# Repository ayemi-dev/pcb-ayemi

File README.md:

# Placas abiertas de Ayemi

Tres placas educativas de hardware libre, una por familia de microcontrolador. Cada una ya trae soldados LED, botones, zumbador, perilla y sensores, y tiene conectores de 4 pines para módulos. Aquí está todo para estudiarlas, modificarlas o fabricarlas: KiCad, Gerber, lista de piezas, firmware de demostración y las herramientas que las generan.

Fichas y renders: [ayemi.org/pcb](https://ayemi.org/pcb)

| Placa | Para quién | Micro | Medida | Carpeta |
|---|---|---|---|---|
| **Chispa por Ayemi** | De 10 a 15 años | ATmega328P (compatible con el IDE de Arduino, placa Uno) | 90 × 60 mm | [`placas/entrenamiento-328p`](placas/entrenamiento-328p) |
| **Enlace por Ayemi** | Secundaria y preparatoria | ESP32-S3 con WiFi y Bluetooth LE, sensor de temperatura y humedad | 90 × 60 mm | [`placas/enlace-esp32s3`](placas/enlace-esp32s3) |
| **Impulso por Ayemi** | Universidad | STM32F411 con USB nativo, SWD, sensor de movimiento y microSD | 100 × 70 mm | [`placas/impulso-stm32`](placas/impulso-stm32) |

## Estado

Las tres están en **Diseño completo**: el esquemático y la placa pasan las revisiones de KiCad (ERC y DRC) sin errores, tienen renders y su firmware de demostración compila. **Todavía no se han fabricado ni probado en físico.** Antes de pedirlas, lee la sección «Pendiente antes de fabricar» del README de cada placa.

| Peldaño | Qué significa |
|---|---|
| Diseño completo | ERC y DRC en 0, renders y firmware que compila |
| Diseño verificado | Además, el análisis DFM de JLCPCB aprobado: lista para fabricar |
| Fabricada y probada | Fabricada y probada en banco con su firmware |

## Qué hay en cada placa

| Carpeta | Contenido |
|---|---|
| `README.md` | Mapa de pines, conectores, cómo programarla y avisos |
| `*.kicad_sch`, `*.kicad_pcb` | Proyecto de KiCad 10 |
| `spec/` | La fuente de verdad: cada hoja del esquemático y la placa descritas en YAML |
| `lib/` | Huellas y modelos 3D propios |
| `fab/v0.1/` | Gerber, BOM y CPL para JLCPCB, esquemático en PDF y serigrafía a escala 1:1 |
| `firmware/` | Demo y prueba de las salidas |
| `docs/` | Diagrama de pines y renders |
| `reportes/` | ERC, DRC, existencias de las piezas, ruteo y modelos 3D |

## Cómo se generan

Las placas no se dibujan a mano: los scripts de `tools/` leen los YAML de `spec/` y generan el esquemático, colocan y rutean la placa, ponen la serigrafía y sacan los archivos de fabricación. Necesitas KiCad 10 y Python 3.12 con `pyyaml` y `segno`. Los pasos exactos de cada placa están en su README, en «Cómo fabricarla».

## Licencias

- Hardware (esquemáticos, placa, Gerber, BOM, modelos 3D): [CERN-OHL-S-2.0](LICENSES/CERN-OHL-S-2.0.txt)
- Firmware y ejemplos: [MIT](LICENSES/MIT.txt)
- Documentación: [CC BY-SA 4.0](LICENSES/CC-BY-SA-4.0.txt)

El nombre y el logotipo **Ayemi** no se incluyen en ninguna de estas licencias: quedan reservados. Detalle en [`LICENSES/LEEME.md`](LICENSES/LEEME.md).

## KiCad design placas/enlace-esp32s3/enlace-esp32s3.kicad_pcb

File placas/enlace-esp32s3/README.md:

# Enlace por Ayemi · v0.1 (ESP32-S3)

**Enlace por Ayemi** es una placa de 90 × 60 mm, de dos capas, para secundaria y preparatoria: lleva un módulo ESP32-S3-WROOM-1-N8 con WiFi y Bluetooth LE, USB-C directo al micro, un sensor de temperatura y humedad SHT40, y ya trae soldados tres LED, un LED RGB, dos botones, un zumbador, una perilla y un sensor de luz. Tiene cinco conectores de 4 pines (I2C 1, I2C 2, SERIE, ANALÓGICO 1 y 2), un conector para pantalla OLED y dos headers con los pines libres. Se programa desde el IDE de Arduino con el núcleo `esp32` de Espressif.

## Estado de la versión 0.1

| Punto | Estado |
|---|---|
| Esquemático (ERC) | 0 errores y 0 advertencias |
| Placa (DRC, con paridad contra el esquemático) | 0 errores, 0 conexiones sin hacer; 2 advertencias de serigrafía justificadas en `spec/drc_justificaciones.yaml` |
| BOM y CPL | 34 números de LCSC (15 Basic y 19 Extended) y 65 componentes; todos con existencia para 50 placas (consulta del 2026-11-02, `reportes/existencias.md`) |
| Renders | Cuatro, con fondo transparente: `superior`, `inferior`, `isometrico` y `portada` (3168 px de ancho, a 45°), en `docs/renders/`. Todas las piezas tienen modelo 3D; siete son cajas o cilindros sencillos (`reportes/modelos3d.md`) |
| Firmware de demo | Compila para «ESP32S3 Dev Module» con USB CDC: 947 953 bytes de flash (72 %) y 42 976 de RAM (13 %). No se ha probado en una placa |
| QR de la cara inferior | Se lee en el render y devuelve `https://ayemi.org/p/esp32` |

**Estado: Diseño completo.** Cumple ERC en 0, DRC en 0, renders completos y firmware que compila. No es «Diseño verificado» (falta el análisis DFM de JLCPCB con su captura) ni «Fabricada y probada» (no hay placa física). No se fabrica por ahora.

## Pendiente antes de fabricar

El rigor que se dejó para después del cierre rápido. Nada de esto está hecho, y la placa no debe fabricarse sin resolverlo:

1. **Antena.** El módulo está a 90 × 60 mm con la antena hacia el borde inferior y una zona sin cobre de 19.6 × 7.7 mm bajo ella, en las dos caras. La hoja del módulo pide 15 mm de aire alrededor de la antena y aquí no se cumplen: el USB-C queda a la izquierda y el DIP a la derecha, ambos a pocos milímetros. El alcance del WiFi hay que medirlo en una placa real.
2. **Huellas locales.** `lib/ayemi.pretty/` trae dos copias de huellas oficiales de KiCad: el módulo, sin las vías térmicas de 0.2 mm (bajo el mínimo de 0.3 mm de JLCPCB), sin la zona de exclusión de cobre y con la cortesía reducida al cuerpo; y el SHT40, sin su zona de exclusión de cobre en la cara superior. Sin esa zona hay pistas pegadas al sensor y el módulo calienta la placa: la lectura de temperatura saldrá alta y hay que medir cuánto.
3. **Hojas de datos.** Leídas solo las de los LED KT-0603-R, -G y -Y (copia de rcscomponents.kiev.ua) y la del TEMT6000X01. No leídas: ESP32-S3-WROOM-1, AP7361C, SHT40, USBLC6, S8050, 2N7002 (falta confirmar que 3.3 V de compuerta lo enciende del todo, su `Vgs(th)` máximo) ni el RGB SZYY1209RGB-B. La Vf del LED verde amarillento KT-0603YG (C2289) y la del RGB salen del listado de JLCPCB, porque lcsc.com no dejó descargar sus hojas.
4. **Huellas provisionales**, a comparar con la hoja de datos o con la pieza física: RGB (D304: huella Avago PLCC4, pero el SZYY1209RGB-B de 3.2 × 2.7 mm tiene dimensiones inconsistentes con su nombre; orden de pines y pin 1 sin comprobar), fototransistor (Q302: polaridad del 1206), zumbador (BZ301), DIP (SW303: patrón del Omron A6S para la pieza Hanbo DO-10PT) y los conectores JST de 4 pines. Lista en `fab/v0.1/revisar_preview_v0.1.txt`.
5. **Modelos 3D sencillos.** USB-C, conectores JST, zumbador, potenciómetro, RGB, Q302 y SHT40 son cajas o cilindros; las medidas salen de la huella o de listados de distribuidor (fuentes en `reportes/modelos3d.md`). Las alturas del RGB (1.9 mm), del SHT40 (0.5 mm) y del zumbador (3.0 mm) son estimadas.
6. **Potencia.** El regulador AP7361C en SOT-223R disipa hasta 0.81 W en un pico de WiFi con `θJA` supuesto de 100 °C/W; el pico total (0.49 A) queda en el límite del PTC de 500 mA. Hay que medir ambos.
7. **USB.** D+ y D− van con pista de 0.2 mm en una ventana fina junto al conector; no se midió su longitud ni su impedancia.
8. **JLCPCB.** Falta subir los Gerber, la BOM y la CPL: análisis DFM con captura, vista previa del ensamblado (rotación de cada pieza en `rotacion_jlc`, hoy vacío), cotización y la decisión sobre el ensamblado de agujero pasante (J406, J407, J408 y RV301).
9. **Impresión a 1:1** de `fab/v0.1/serigrafia_1a1_v0.1_superior.pdf` e `_inferior.pdf`. Rótulos de 1.0 mm de alto. Emi va en versión de cabeza.
10. **Firmware y pruebas.** El demo solo se compiló. Faltan la prueba en placa, el proyecto de Wokwi y la pantalla OLED (el conector PANTALLA no tiene ejemplo).

## Mapa de pines

Con los diez interruptores del DIP (SW303; nueve en uso, la posición 10 queda sin conexión) en ON, cada periférico queda conectado a su pin. Con el interruptor en OFF, el pin queda libre para cables o módulos.

| Periférico | Pin | Posición del DIP | Notas |
|---|---|---|---|
| LED rojo | IO10 | 1 | |
| LED verde amarillento | IO11 | 2 | |
| LED amarillo | IO12 | 3 | |
| RGB rojo | IO13 | 4 | Ánodo común a 5 V, un 2N7002 por canal: pin en alto = encendido; PWM con `analogWrite` |
| RGB verde | IO14 | 5 | |
| RGB azul | IO15 | 6 | |
| Botón A | IO16 | 7 | 330 Ω en serie, sin pull-up externo: usa `INPUT_PULLUP`; vale 0 al pulsar |
| Botón B | IO17 | 8 | Igual que el A |
| Zumbador | IO18 | 9 | A la base de un S8050, desde 5 V; con `tone()` |
| Perilla | IO1 | sin DIP | ADC1, 1 kΩ en serie |
| Sensor de luz (TEMT6000) | IO2 | sin DIP | ADC1; más luz, más voltaje |
| SHT40 | IO8 (SDA), IO9 (SCL) | sin DIP | I2C, dirección 0x44, siempre conectado al bus |
| BOOT / RESET | IO0 / EN | botones | |

### Conectores

| Conector | Pines (de 1 a 4) |
|---|---|
| I2C 1 e I2C 2 (J401, J402, en paralelo) | SCL (IO9), SDA (IO8), 3V3, GND |
| SERIE (J403) | RX (IO44), TX (IO43), 3V3, GND |
| ANALÓGICO 1 (J404) | IO4, IO5, 3V3, GND |
| ANALÓGICO 2 (J405) | IO6, IO7, 3V3, GND |
| PANTALLA (J406, header de 4) | GND, 3V3, SCL (IO9), SDA (IO8) |
| IO A (J407, header de 10) | IO10 a IO18 y GND |
| IO B (J408, header de 12) | IO21, IO38, IO39, IO40, IO41, IO42, IO47, IO48, 3V3, 5V, GND, GND |

Pines que no salen a ningún lado: IO3, IO35 a IO37, IO45 e IO46 (de arranque o de la memoria del módulo). El diagrama de pines está en `docs/diagrama_pines.svg` y los renders en `docs/renders/`.

## Cómo programarla

1. Instala el IDE de Arduino y, desde el gestor de placas, el paquete **esp32** de Espressif (probado con 3.0.3).
2. Conecta la placa con un cable USB-C. Para cargar el primer programa mantén BOOT, pulsa RESET y suelta ambos.
3. En el IDE elige la placa «ESP32S3 Dev Module», con **USB CDC On Boot: Enabled**, y el puerto que aparece.
4. Abre `firmware/enlace_demo/enlace_demo.ino` y súbelo. Abre el monitor serie a 115200 baudios.

El demo prueba las salidas al encender, crea la red WiFi `Enlace-XXXX` (sin contraseña) y muestra en `http://192.168.4.1` la perilla, la luz, la temperatura, la humedad y los botones, y deja encender los LED, elegir el color del RGB y hacer sonar el zumbador.

Por línea de comandos: `arduino-cli compile --fqbn esp32:esp32:esp32s3:CDCOnBoot=cdc firmware/enlace_demo`.

## Avisos

- **Reservado: no uses IO19 ni IO20** (son el USB), ni IO0, IO3, IO45 e IO46 (arranque).
- **Conector SERIE.** Usa el UART0 (IO43 e IO44). Con USB CDC al arrancar, el monitor serie sale por el USB y el UART0 queda libre.
- **DIP en ON.** IO10 a IO18 quedan cargados por el periférico. Si conectas un módulo a uno de esos pines, pon su interruptor en OFF.
- **5 V.** Salen del USB después de un PTC de 500 mA. Los pines de datos son de 3.3 V y no toleran 5 V.
- **WiFi y consumo.** Un pico de transmisión pide hasta 355 mA al módulo. Con un cable largo o un hub el puerto puede entregar menos de 5 V.

## Cómo fabricarla

La fuente de verdad son los YAML de `spec/`. Los scripts de `tools/` generan y verifican todo lo demás; con KiCad cerrado:

```powershell
py -3.12 -P tools/gen_hoja.py placas/enlace-esp32s3 --todas       # esquemático
py -3.12 -P tools/erc.py placas/enlace-esp32s3                    # ERC
py -3.12 -P tools/huellas_locales.py placas/enlace-esp32s3        # copias ajustadas de huellas
powershell -File tools/construir_placa.ps1 -Placa placas/enlace-esp32s3 -Setup   # colocar, rutear, costura, serigrafía (30 a 40 min)
py -3.12 -P tools/drc.py placas/enlace-esp32s3                    # DRC
py -3.12 -P tools/fab.py placas/enlace-esp32s3                    # Gerber, BOM, CPL, PDF
py -3.12 -P tools/verificar_existencias.py placas/enlace-esp32s3
py -3.12 -P tools/renders.py placas/enlace-esp32s3                # superior, inferior, isométrico y portada
```

En `fab/v0.1/` quedan `gerbers_v0.1.zip`, `bom_jlc_v0.1.csv`, `cpl_jlc_v0.1.csv`, `esquematico_v0.1.pdf`, `revisar_preview_v0.1.txt` y los PDF de serigrafía a escala 1:1. La placa es de 2 capas, FR-4 de 1.6 mm, máscara negra y serigrafía blanca.

## Carpetas

| Carpeta | Contenido |
|---|---|
| `spec/` | YAML de cada hoja y de la placa; `logos/` con el logotipo, Emi y el QR |
| `lib/ayemi.pretty/` | Huellas locales (módulo y SHT40) |
| `lib/ayemi.3dshapes/` | Modelos 3D sencillos (`.wrl`) de las piezas sin modelo |
| `fab/v0.1/` | Archivos para JLCPCB y serigrafía 1:1 |
| `firmware/enlace_demo/` | Demo y prueba de fábrica |
| `docs/` | Diagrama de pines y renders |
| `reportes/` | ERC, DRC, existencias, ruteo y 3D |

## Licencias

- Hardware (esquemáticos, placa, Gerber, BOM, modelos 3D): CERN-OHL-S-2.0 (`../../LICENSES/CERN-OHL-S-2.0.txt`).
- Firmware y ejemplos: MIT (`firmware/LICENSE` y `../../LICENSES/MIT.txt`).
- Documentación y guías: CC BY-SA 4.0 (`../../LICENSES/CC-BY-SA-4.0.txt`).

El nombre y el logotipo **Ayemi** no se incluyen en ninguna de estas licencias: quedan reservados.

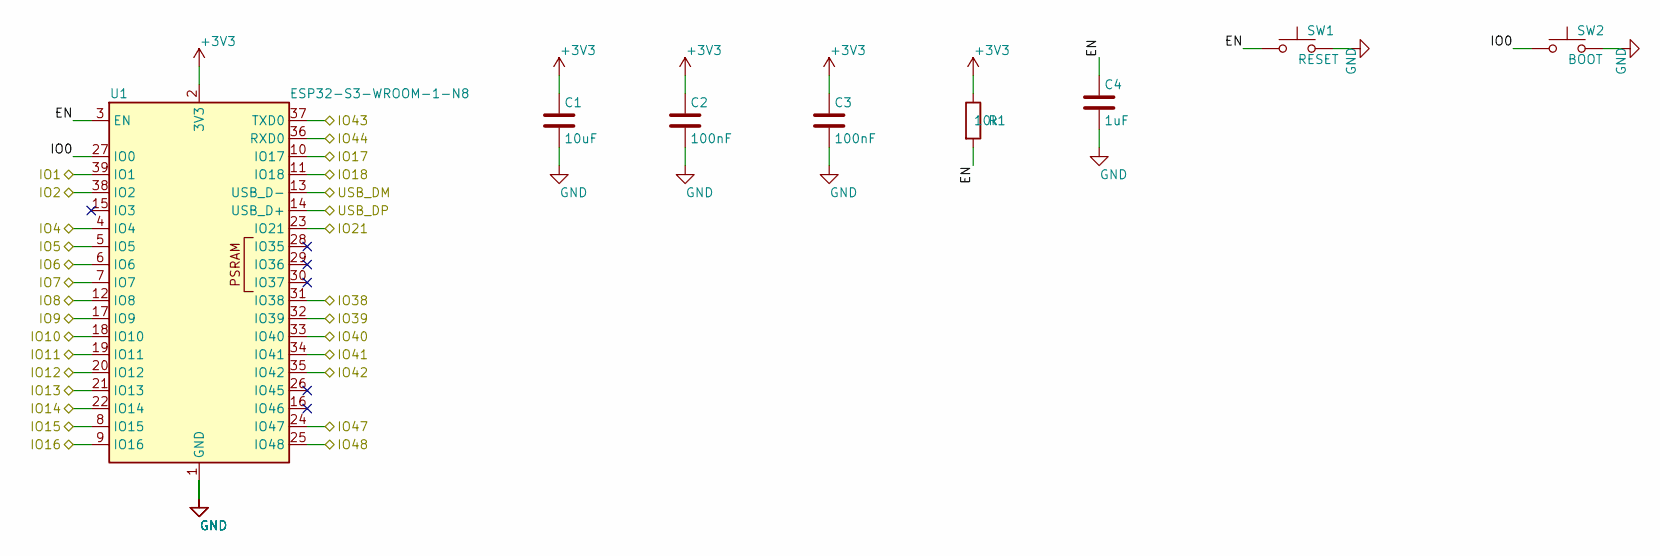
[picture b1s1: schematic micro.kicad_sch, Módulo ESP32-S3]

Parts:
C1: 10uF; C_0603_1608Metric; LCSC C19702
C2, C3: 100nF; C_0603_1608Metric; LCSC C14663
C4: 1uF; C_0603_1608Metric; LCSC C15849
R1: 10k; R_0603_1608Metric; LCSC C25804
SW1: RESET; SW_Push_1TS009xxxx-xxxx-xxxx_6x6x5mm; LCSC C319409
SW2: BOOT; SW_Push_1TS009xxxx-xxxx-xxxx_6x6x5mm; LCSC C319409
U1: ESP32-S3-WROOM-1-N8; ESP32-S3-WROOM-1_ayemi; LCSC C2913198

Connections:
+3V3: C1.1, C2.1, C3.1, R1.1, U1.2 (3V3); also elsewhere on the board
/IO1: U1.39 (IO1); also elsewhere on the board
/IO2: U1.38 (IO2); also elsewhere on the board
/IO4: U1.4 (IO4); also elsewhere on the board
/IO5: U1.5 (IO5); also elsewhere on the board
/IO6: U1.6 (IO6); also elsewhere on the board
/IO7: U1.7 (IO7); also elsewhere on the board
/IO8: U1.12 (IO8); also elsewhere on the board
/IO9: U1.17 (IO9); also elsewhere on the board
/IO10: U1.18 (IO10); also elsewhere on the board
/IO11: U1.19 (IO11); also elsewhere on the board
/IO12: U1.20 (IO12); also elsewhere on the board
/IO13: U1.21 (IO13); also elsewhere on the board
/IO14: U1.22 (IO14); also elsewhere on the board
/IO15: U1.8 (IO15); also elsewhere on the board
/IO16: U1.9 (IO16); also elsewhere on the board
/IO17: U1.10 (IO17); also elsewhere on the board
/IO18: U1.11 (IO18); also elsewhere on the board
/IO21: U1.23 (IO21); also elsewhere on the board
/IO38: U1.31 (IO38); also elsewhere on the board
/IO39: U1.32 (IO39); also elsewhere on the board
/IO40: U1.33 (IO40); also elsewhere on the board
/IO41: U1.34 (IO41); also elsewhere on the board
/IO42: U1.35 (IO42); also elsewhere on the board
/IO43: U1.37 (TXD0); also elsewhere on the board
/IO44: U1.36 (RXD0); also elsewhere on the board
/IO47: U1.24 (IO47); also elsewhere on the board
/IO48: U1.25 (IO48); also elsewhere on the board
/USB_DM: U1.13 (USB_D-); also elsewhere on the board
/USB_DP: U1.14 (USB_D+); also elsewhere on the board
/micro/EN: C4.1, R1.2, SW1.1, U1.3 (EN)
/micro/IO0: SW2.1, U1.27 (IO0)
GND: C1.2, C2.2, C3.2, C4.2, SW1.2, SW2.2, U1.1 (GND), U1.40 (GND), U1.41 (GND); also elsewhere on the board

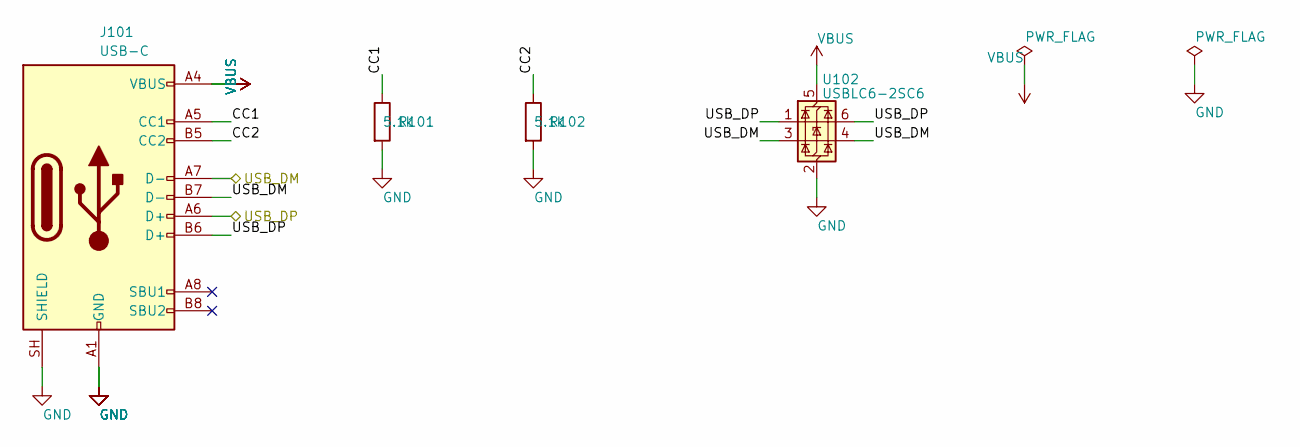
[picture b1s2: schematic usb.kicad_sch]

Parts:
J101: USB-C; USB_C_Receptacle_HRO_TYPE-C-31-M-12; LCSC C165948
R101, R102: 5.1k; R_0603_1608Metric; LCSC C23186
U102: USBLC6-2SC6; SOT-23-6; LCSC C7519

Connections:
/USB_DM: J101.A7 (D-), J101.B7 (D-), U102.3 (I/O2), U102.4 (I/O2); also elsewhere on the board
/USB_DP: J101.A6 (D+), J101.B6 (D+), U102.1 (I/O1), U102.6 (I/O1); also elsewhere on the board
/usb/CC1: J101.A5 (CC1), R101.1
/usb/CC2: J101.B5 (CC2), R102.1
GND: J101.A1 (GND), J101.A12 (GND), J101.B1 (GND), J101.B12 (GND), J101.SH (SHIELD), R101.2, R102.2, U102.2 (GND); also elsewhere on the board
VBUS: J101.A4 (VBUS), J101.A9 (VBUS), J101.B4 (VBUS), J101.B9 (VBUS), U102.5 (VBUS); also elsewhere on the board

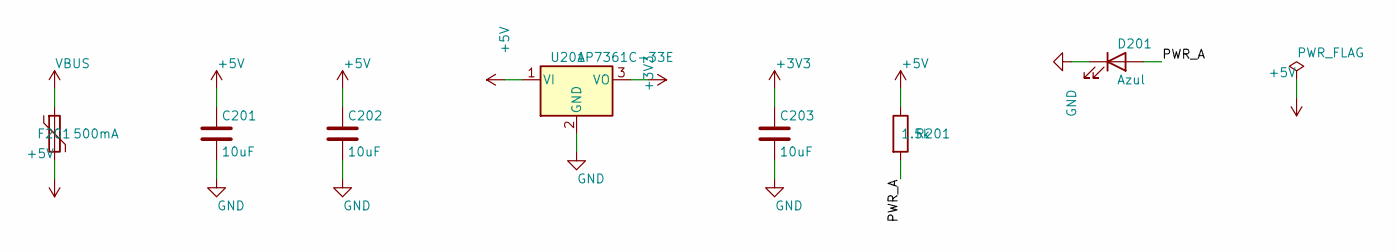
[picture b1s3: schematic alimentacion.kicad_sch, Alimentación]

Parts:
C201, C202, C203: 10uF; C_0603_1608Metric; LCSC C19702
D201: Azul; LED_0603_1608Metric; LCSC C2288
F201: 500mA; Fuse_1206_3216Metric; LCSC C163512
R201: 1.5k; R_0603_1608Metric; LCSC C22843
U201: AP7361C-33E; SOT-223-3_TabPin2; LCSC C3743528

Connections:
+3V3: C203.1, U201.3 (VO); also elsewhere on the board
+5V: C201.1, C202.1, F201.2, R201.1, U201.1 (VI); also elsewhere on the board
/alimentacion/PWR_A: D201.2 (A), R201.2
GND: C201.2, C202.2, C203.2, D201.1 (K), U201.2 (GND); also elsewhere on the board
VBUS: F201.1; also elsewhere on the board

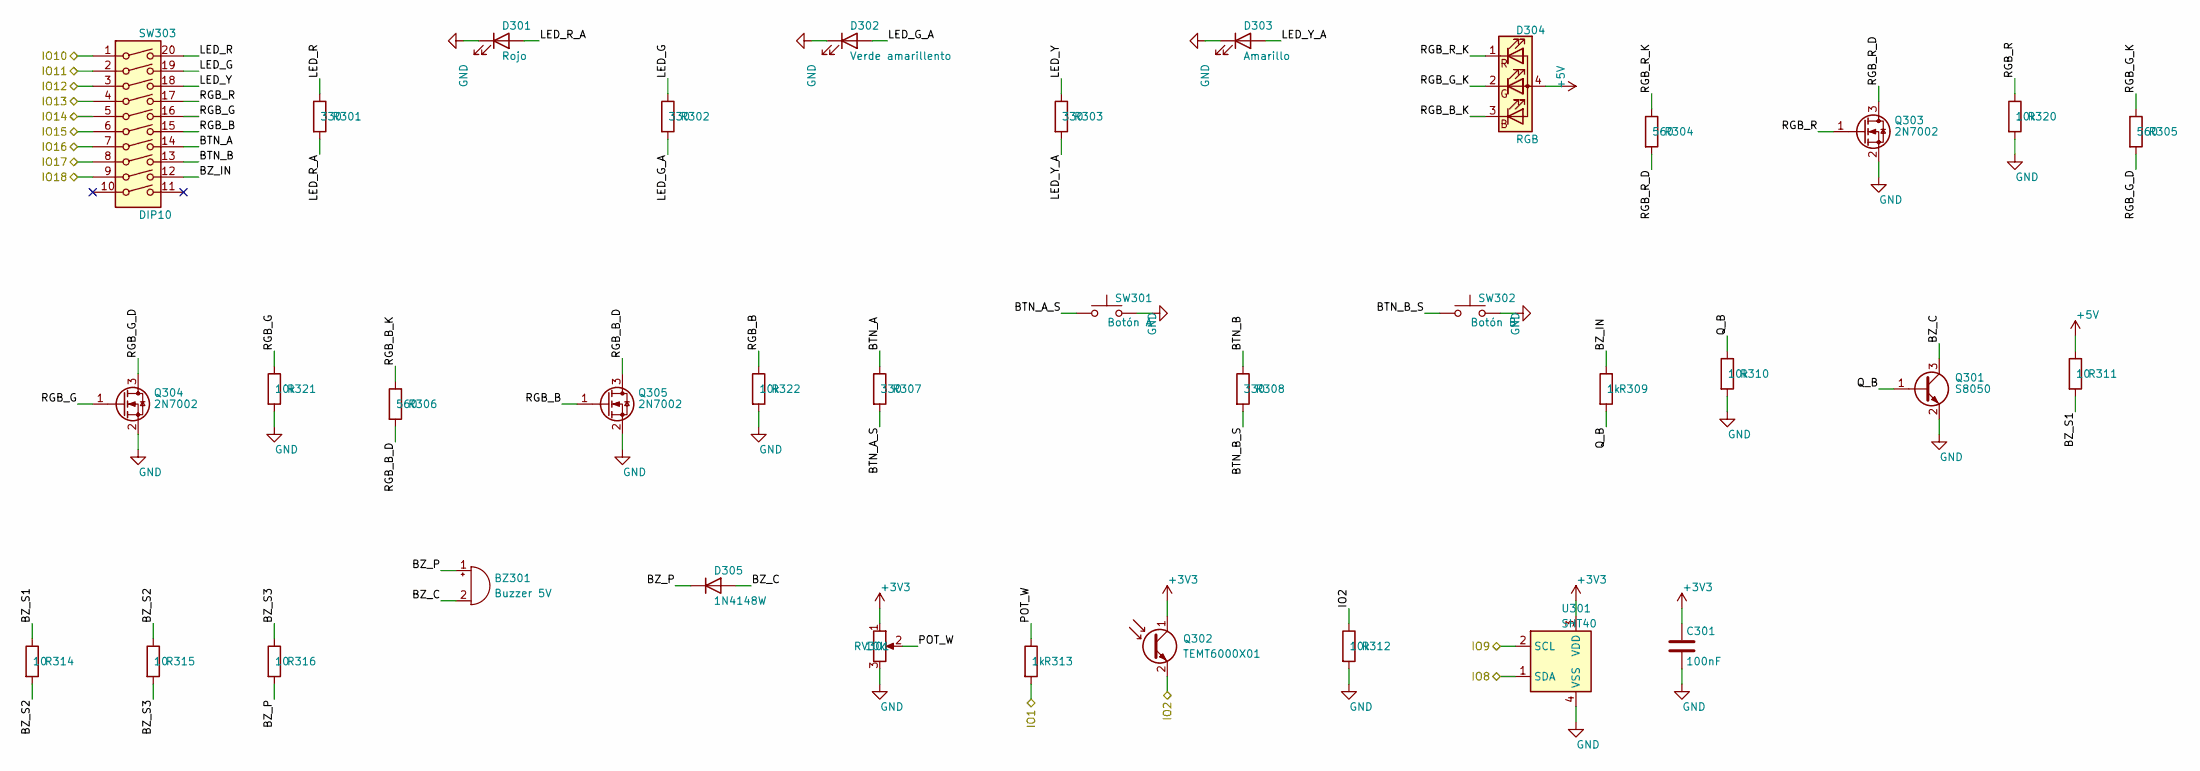
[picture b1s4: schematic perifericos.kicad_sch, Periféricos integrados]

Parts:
BZ301: Buzzer 5V; MagneticBuzzer_CUI_CMT-8504-100-SMT; LCSC C7421674
C301: 100nF; C_0603_1608Metric; LCSC C14663
D301: Rojo; LED_0603_1608Metric; LCSC C2286
D302: Verde amarillento; LED_0603_1608Metric; LCSC C2289
D303: Amarillo; LED_0603_1608Metric; LCSC C2287
D304: RGB; LED_Avago_PLCC4_3.2x2.8mm_CW; LCSC C3029073
D305: 1N4148W; D_SOD-123; LCSC C81598
Q301: S8050; SOT-23; LCSC C2146
Q302: TEMT6000X01; LED_1206_3216Metric; LCSC C94098
Q303, Q304, Q305: 2N7002; SOT-23; LCSC C8545
R301, R302, R303, R307, R308: 330; R_0603_1608Metric; LCSC C23138
R304, R305, R306: 560; R_0603_1608Metric; LCSC C23204
R309, R313: 1k; R_0603_1608Metric; LCSC C21190
R310, R312, R320, R321, R322: 10k; R_0603_1608Metric; LCSC C25804
R311, R314, R315, R316: 10; R_0603_1608Metric; LCSC C22859
RV301: 10k; Potentiometer_Alps_RK09K_Single_Vertical; LCSC C202373
SW301: Botón A; SW_Push_1TS009xxxx-xxxx-xxxx_6x6x5mm; LCSC C319409
SW302: Botón B; SW_Push_1TS009xxxx-xxxx-xxxx_6x6x5mm; LCSC C319409
SW303: DIP10; SW_DIP_SPSTx10_Slide_Omron_A6S-1010x_W8.9mm_P2.54mm; LCSC C18198122
U301: SHT40; SHT4x_ayemi; LCSC C2909890

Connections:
+3V3: C301.1, Q302.1 (C), RV301.1, U301.3 (VDD); also elsewhere on the board
+5V: D304.4 (A), R311.1; also elsewhere on the board
/IO1: R313.2; also elsewhere on the board
/IO2: Q302.2 (E), R312.1; also elsewhere on the board
/IO8: U301.1 (SDA); also elsewhere on the board
/IO9: U301.2 (SCL); also elsewhere on the board
/IO10: SW303.1; also elsewhere on the board
/IO11: SW303.2; also elsewhere on the board
/IO12: SW303.3; also elsewhere on the board
/IO13: SW303.4; also elsewhere on the board
/IO14: SW303.5; also elsewhere on the board
/IO15: SW303.6; also elsewhere on the board
/IO16: SW303.7; also elsewhere on the board
/IO17: SW303.8; also elsewhere on the board
/IO18: SW303.9; also elsewhere on the board
/perifericos/BTN_A: R307.1, SW303.14
/perifericos/BTN_A_S: R307.2, SW301.1
/perifericos/BTN_B: R308.1, SW303.13
/perifericos/BTN_B_S: R308.2, SW302.1
/perifericos/BZ_C: BZ301.2 (-), D305.2 (A), Q301.3 (C)
/perifericos/BZ_IN: R309.1, SW303.12
/perifericos/BZ_P: BZ301.1 (+), D305.1 (K), R316.2
/perifericos/BZ_S1: R311.2, R314.1
/perifericos/BZ_S2: R314.2, R315.1
/perifericos/BZ_S3: R315.2, R316.1
/perifericos/LED_G: R302.1, SW303.19
/perifericos/LED_G_A: D302.2 (A), R302.2
/perifericos/LED_R: R301.1, SW303.20
/perifericos/LED_R_A: D301.2 (A), R301.2
/perifericos/LED_Y: R303.1, SW303.18
/perifericos/LED_Y_A: D303.2 (A), R303.2
/perifericos/POT_W: R313.1, RV301.2
/perifericos/Q_B: Q301.1 (B), R309.2, R310.1
/perifericos/RGB_B: Q305.1 (G), R322.1, SW303.15
/perifericos/RGB_B_D: Q305.3 (D), R306.2
/perifericos/RGB_B_K: D304.3 (BK), R306.1
/perifericos/RGB_G: Q304.1 (G), R321.1, SW303.16
/perifericos/RGB_G_D: Q304.3 (D), R305.2
/perifericos/RGB_G_K: D304.2 (GK), R305.1
/perifericos/RGB_R: Q303.1 (G), R320.1, SW303.17
/perifericos/RGB_R_D: Q303.3 (D), R304.2
/perifericos/RGB_R_K: D304.1 (RK), R304.1
GND: C301.2, D301.1 (K), D302.1 (K), D303.1 (K), Q301.2 (E), Q303.2 (S), Q304.2 (S), Q305.2 (S), R310.2, R312.2, R320.2, R321.2, R322.2, RV301.3, SW301.2, SW302.2, U301.4 (VSS); also elsewhere on the board

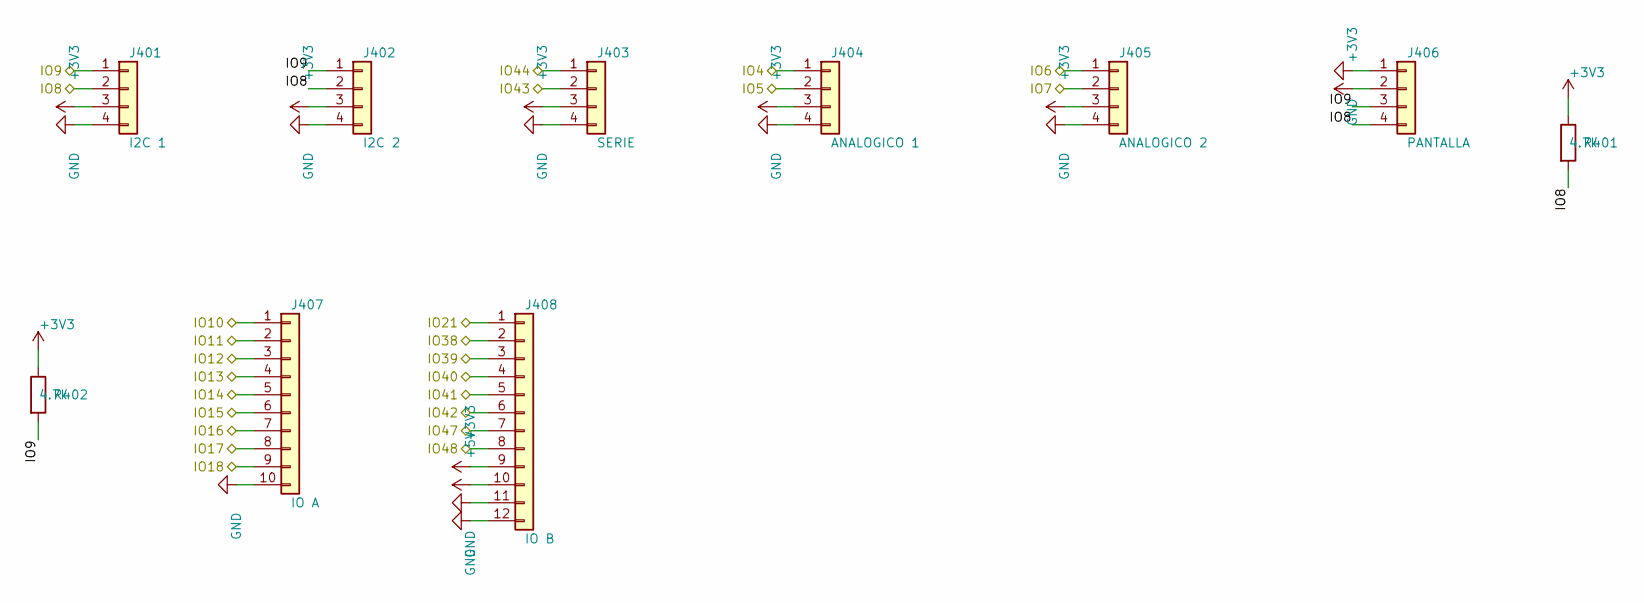
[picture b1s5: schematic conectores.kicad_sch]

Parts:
J401: I2C 1; JST_PH_S4B-PH-SM4-TB_1x04-1MP_P2.00mm_Horizontal; LCSC C265102
J402: I2C 2; JST_PH_S4B-PH-SM4-TB_1x04-1MP_P2.00mm_Horizontal; LCSC C265102
J403: SERIE; JST_PH_S4B-PH-SM4-TB_1x04-1MP_P2.00mm_Horizontal; LCSC C265102
J404: ANALOGICO 1; JST_PH_S4B-PH-SM4-TB_1x04-1MP_P2.00mm_Horizontal; LCSC C265102
J405: ANALOGICO 2; JST_PH_S4B-PH-SM4-TB_1x04-1MP_P2.00mm_Horizontal; LCSC C265102
J406: PANTALLA; PinHeader_1x04_P2.54mm_Vertical; LCSC C492403
J407: IO A; PinHeader_1x10_P2.54mm_Vertical; LCSC C492409
J408: IO B; PinHeader_1x12_P2.54mm_Vertical; LCSC C2840012
R401, R402: 4.7k; R_0603_1608Metric; LCSC C23162

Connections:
+3V3: J401.3, J402.3, J403.3, J404.3, J405.3, J406.2, J408.9, R401.1, R402.1; also elsewhere on the board
+5V: J408.10; also elsewhere on the board
/IO4: J404.1; also elsewhere on the board
/IO5: J404.2; also elsewhere on the board
/IO6: J405.1; also elsewhere on the board
/IO7: J405.2; also elsewhere on the board
/IO8: J401.2, J402.2, J406.4, R401.2; also elsewhere on the board
/IO9: J401.1, J402.1, J406.3, R402.2; also elsewhere on the board
/IO10: J407.1; also elsewhere on the board
/IO11: J407.2; also elsewhere on the board
/IO12: J407.3; also elsewhere on the board
/IO13: J407.4; also elsewhere on the board
/IO14: J407.5; also elsewhere on the board
/IO15: J407.6; also elsewhere on the board
/IO16: J407.7; also elsewhere on the board
/IO17: J407.8; also elsewhere on the board
/IO18: J407.9; also elsewhere on the board
/IO21: J408.1; also elsewhere on the board
/IO38: J408.2; also elsewhere on the board
/IO39: J408.3; also elsewhere on the board
/IO40: J408.4; also elsewhere on the board
/IO41: J408.5; also elsewhere on the board
/IO42: J408.6; also elsewhere on the board
/IO43: J403.2; also elsewhere on the board
/IO44: J403.1; also elsewhere on the board
/IO47: J408.7; also elsewhere on the board
/IO48: J408.8; also elsewhere on the board
GND: J401.4, J402.4, J403.4, J404.4, J405.4, J406.1, J407.10, J408.11, J408.12; also elsewhere on the board

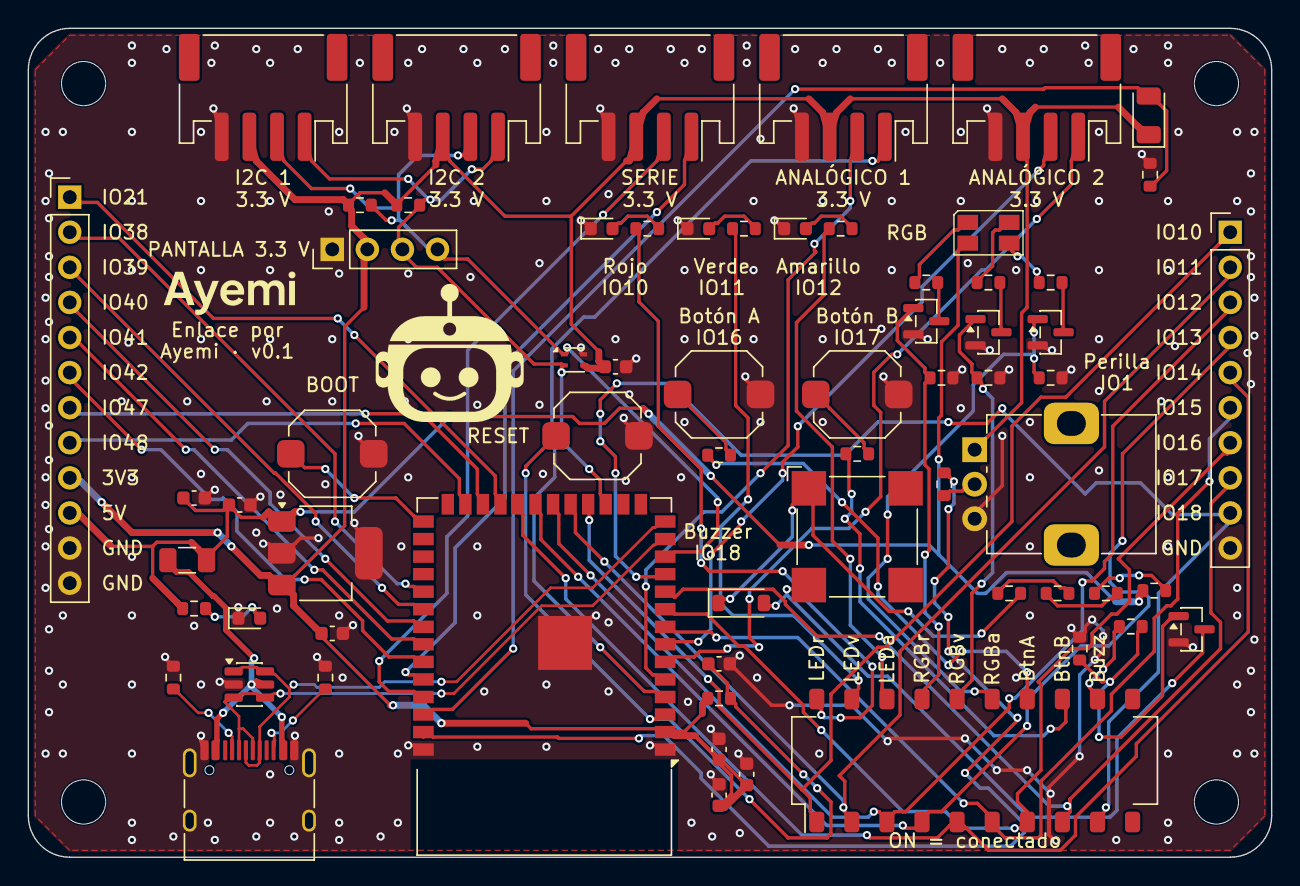
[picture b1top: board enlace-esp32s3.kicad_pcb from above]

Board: 2 copper layers, 90.0 x 60.0 mm, 69 parts (0 on the bottom side), 65 nets.

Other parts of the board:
H1, H2, H3, H4: M3; MountingHole_3.2mm_M3

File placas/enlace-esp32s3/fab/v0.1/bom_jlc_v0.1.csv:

Comment,Designator,Footprint,LCSC Part #,Clase,Alternativa
Buzzer 5V,BZ301,MagneticBuzzer_CUI_CMT-8504-100-SMT,C7421674,Extended,C530411
10uF,"C1,C201,C202,C203",C_0603_1608Metric,C19702,Basic,C380314
100nF,"C2,C3,C301",C_0603_1608Metric,C14663,Basic,C91183
1uF,C4,C_0603_1608Metric,C15849,Basic,C106214
Azul,D201,LED_0603_1608Metric,C2288,Extended,C84266
Rojo,D301,LED_0603_1608Metric,C2286,Basic,C84263
Verde amarillento,D302,LED_0603_1608Metric,C2289,Extended,C84268
Amarillo,D303,LED_0603_1608Metric,C2287,Extended,C84268
RGB,D304,LED_Avago_PLCC4_3.2x2.8mm_CW,C3029073,Extended,C3029071
1N4148W,D305,D_SOD-123,C81598,Basic,C2099
500mA,F201,Fuse_1206_3216Metric,C163512,Extended,C49318356
USB-C,J101,USB_C_Receptacle_HRO_TYPE-C-31-M-12,C165948,Extended,C5337088
C265102,"J401,J402,J403,J404,J405",JST_PH_S4B-PH-SM4-TB_1x04-1MP_P2.00mm_Horizontal,C265102,Extended,C7429571
PANTALLA,J406,PinHeader_1x04_P2.54mm_Vertical,C492403,Extended,C2691448
IO A,J407,PinHeader_1x10_P2.54mm_Vertical,C492409,Extended,C41425300
IO B,J408,PinHeader_1x12_P2.54mm_Vertical,C2840012,Extended,C54803345
S8050,Q301,SOT-23,C2146,Basic,C105433
TEMT6000X01,Q302,LED_1206_3216Metric,C94098,Extended,C47416518
2N7002,"Q303,Q304,Q305",SOT-23,C8545,Basic,C12779
10k,"R1,R310,R312,R320,R321,R322",R_0603_1608Metric,C25804,Basic,C98220
5.1k,"R101,R102",R_0603_1608Metric,C23186,Basic,C105580
1.5k,R201,R_0603_1608Metric,C22843,Basic,C114668
330,"R301,R302,R303,R307,R308",R_0603_1608Metric,C23138,Basic,C105881
560,"R304,R305,R306",R_0603_1608Metric,C23204,Basic,C114629
1k,"R309,R313",R_0603_1608Metric,C21190,Basic,C22548
10,"R311,R314,R315,R316",R_0603_1608Metric,C22859,Basic,C109318
4.7k,"R401,R402",R_0603_1608Metric,C23162,Basic,C99782
10k,RV301,Potentiometer_Alps_RK09K_Single_Vertical,C202373,Extended,C351173
C319409,"SW1,SW2,SW301,SW302",SW_Push_1TS009xxxx-xxxx-xxxx_6x6x5mm,C319409,Extended,C255813
DIP10,SW303,SW_DIP_SPSTx10_Slide_Omron_A6S-1010x_W8.9mm_P2.54mm,C18198122,Extended,C5160858
ESP32-S3-WROOM-1-N8,U1,ESP32-S3-WROOM-1_ayemi,C2913198,Extended,C2913197
USBLC6-2SC6,U102,SOT-23-6,C7519,Extended,C2687116
AP7361C-33E,U201,SOT-223-3_TabPin2,C3743528,Extended,C150716
SHT40,U301,SHT4x_ayemi,C2909890,Extended,C2848306

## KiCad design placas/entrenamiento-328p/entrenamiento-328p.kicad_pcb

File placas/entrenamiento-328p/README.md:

# Chispa por Ayemi · v0.1 (ATmega328P)

**Chispa por Ayemi** es una placa de 90 × 60 mm, de dos capas, para enseñar programación y electrónica a niños y adolescentes de 10 a 15 años en tres niveles: Explorar (bloques, sin cables), Conectar (módulos de 4 pines) y Construir (código y pines). Lleva un ATmega328P a 16 MHz, USB-C con convertidor CH340C, y ya trae soldados tres LED, un LED RGB, dos botones, un zumbador, un potenciómetro y un sensor de luz. Se programa desde el IDE de Arduino eligiendo la placa «Arduino Uno».

## Estado de la versión 0.1

| Punto | Estado |
|---|---|
| Esquemático (ERC) | 0 errores y 0 advertencias |
| Placa (DRC, con paridad contra el esquemático) | 0 errores, 0 conexiones sin hacer; 2 advertencias de serigrafía justificadas en `spec/drc_justificaciones.yaml` |
| BOM y CPL | 38 números de LCSC (17 Basic y 21 Extended) y 71 componentes; todos con existencia para 50 placas (consulta del 2026-11-01, `reportes/existencias.md`) |
| Renders | Cuatro, con fondo transparente: `superior`, `inferior`, `isometrico` y `portada` (3168 px de ancho, a 45°), en `docs/renders/`. Todas las piezas tienen modelo 3D; seis son cajas sencillas (`reportes/modelos3d.md`) |
| Firmware de prueba | Compila para «Arduino Uno»: 5 322 bytes de flash (16 %) y 234 de RAM (11 %) |
| Wokwi | Proyecto listo; el firmware se probó en `avr8js`. Falta el video en wokwi.com |

**Estado: Diseño completo.** Cumple ERC en 0, DRC en 0, renders completos y firmware que compila. No es «Diseño verificado» (falta el análisis DFM de JLCPCB con su captura) ni «Fabricada y probada» (no hay placa física). No se fabrica por ahora.

## Pendiente antes de fabricar

El rigor que se dejó para después del cierre exprés. Nada de esto está hecho, y la placa no debe fabricarse sin resolverlo:

1. **Hojas de datos.** Leídos y confirmados solo el CH340C (R232, V3, VOL, VCC) y el TEMT6000X01. Faltan el ATmega328P, el USBLC6, la bobina del zumbador, el potenciómetro, el S8050 y las tensiones directas de los LED.
2. **Zumbador.** La huella es la del CUI CMT-8504 (8.5 mm, 4 mm de alto) y la pieza de la BOM es el Fengming YS-SBZ8530C05R30 (C7421674). La bobina que se usó en el cálculo (30 ± 4 Ω) viene de una hoja genérica de buzzers 8530. Falta la hoja de datos de la pieza real, su huella y su altura (el modelo 3D usa 3.0 mm, estimados por el número de parte).
3. **Caída de tensión a 500 mA.** El PTC F201 se eligió para tener 4.50 V en los módulos a 300 mA (resistencia máxima ≤ 0.8 Ω). Falta comprobar la resistencia máxima real de la pieza y calcular el riel a 500 mA.
4. **Huellas provisionales**, a comparar con la hoja de datos o con la pieza física: zumbador (BZ301), LED RGB (D304: orden de pines y pin 1), fototransistor (Q302: polaridad del 1206; montado al revés pone 5 V en el emisor), DIP (SW303: patrón del Omron A6S) y los conectores JST de 4 pines. Lista en `fab/v0.1/revisar_preview_v0.1.txt`.
5. **Modelos 3D sencillos.** USB-C, conectores JST, zumbador, potenciómetro, RGB y Q302 son cajas o cilindros; las medidas salen de la huella o de listados de distribuidor (fuentes en `reportes/modelos3d.md`). El potenciómetro no lleva eje ni perilla. La altura y el choque en 3D no se han medido.
6. **CH340C descontinuado.** JLCPCB lo marca así, aunque hay más de 100 000 en existencia (consulta del 2026-11-01). Plan B: CH340N o CH340K (`reportes/piezas.md`).
7. **JLCPCB.** Falta subir los Gerber, la BOM y la CPL: análisis DFM con captura, vista previa del ensamblado (rotación de cada pieza en `rotacion_jlc`, hoy vacío), cotización y la decisión sobre el ensamblado de agujero pasante (J407, J408, J406, J1 y RV301). Pasos en `docs/pruebas_manuales.md`.
8. **Impresión a 1:1** de `fab/v0.1/serigrafia_1a1_v0.1_superior.pdf` e `_inferior.pdf`. Rótulos de 1.0 mm de alto (el diseño pedía 1.5 mm). Emi va en versión de cabeza porque el cuerpo completo no cabe en la cara superior. Falta además leer el QR con un teléfono sobre la placa impresa.
9. **Cristal y potencia.** XT1 y XT2 miden 11.9 y 9.4 mm (el diseño pedía menos de 8 mm; sin vías, en la cara superior). Las pistas de potencia quedan a 0.25 mm donde no caben a 0.5 mm (0.87 A por IPC-2221 contra 143.8 mA de consumo máximo).
10. **Prueba del conector SERIE** con un módulo real, y **video de Wokwi**. El comando de `avrdude` del bootloader tampoco se ha probado en una placa real.

## Mapa de pines

Con los ocho interruptores del DIP (SW303) en ON, cada periférico queda conectado a su pin. Con el interruptor en OFF, el pin queda libre para cables o módulos.

| Periférico | Pin | Posición del DIP | Notas |
|---|---|---|---|
| Botón A | D2 | 1 | `INPUT_PULLUP`; vale 0 al pulsar |
| Zumbador | D3 | 2 | Con `tone()`; usa el Timer2 |
| Botón B | D4 | 3 | Igual que el A |
| RGB azul | D5 | 4 | Cátodo común; PWM |
| RGB verde | D6 | 5 | PWM |
| LED rojo | D7 | 6 | |
| LED verde | D8 | 7 | |
| RGB rojo | D9 | 8 | PWM |
| LED amarillo «L» | D13 | sin DIP | Comparte el pin con SCK del SPI |
| Potenciómetro | A6 | sin DIP | Solo entrada analógica; 1 kΩ en serie con el cursor |
| Sensor de luz (TEMT6000) | A7 | sin DIP | Solo entrada analógica; más luz, más voltaje |

### Conectores

| Conector | Pines (de 1 a 4) |
|---|---|
| I2C 1 e I2C 2 (J401, J402, en paralelo) | SCL (A5), SDA (A4), 5 V, GND |
| SERIE (J403) | RX (D0), TX (D1), 5 V, GND |
| ANALÓGICO 1 (J404) | A0, A1, 5 V, GND |
| ANALÓGICO 2 (J405) | A2, A3, 5 V, GND |
| SPI (J406, header de 6) | MOSI (D11), MISO (D12), SCK (D13), CS (D10), 5 V, GND |
| D0-D13 (J407, header de 15) | D0 a D13 y GND junto a D13 |
| A0-A7 (J408, header de 12) | A0 a A7, 5 V, 3V3, GND, RESET |
| ICSP (J1, 2 × 3) | MISO, 5 V, SCK, MOSI, RESET, GND |

El diagrama de pines está en `docs/diagrama_pines.svg` y los renders en `docs/renders/`.

## Cómo programarla

1. Instala el IDE de Arduino y el controlador del CH340 si tu sistema no lo trae.
2. Conecta la placa con un cable USB-C. El LED azul indica que hay 5 V.
3. En el IDE elige la placa «Arduino Uno» y el puerto que aparece al conectarla.
4. Abre `firmware/prueba_fabrica/prueba_fabrica.ino`, súbelo y abre el monitor serie a 115200 baudios.

Por línea de comandos, el equivalente es `arduino-cli compile --fqbn arduino:avr:uno firmware/prueba_fabrica`. En esta máquina no está instalado `arduino-cli`, así que `tools/firmware.py` compila con el mismo compilador y el mismo núcleo del IDE:

```powershell
py -3.12 -P tools/firmware.py compilar placas/entrenamiento-328p
```

### Bootloader (placas nuevas)

Un ATmega328P nuevo no trae bootloader. Se graba una vez por ICSP (J1) con un programador y los fusibles de la Uno: low `0xFF`, high `0xDE`, extended `0xFD`, bloqueo final `0x0F`, con el archivo `optiboot/optiboot_atmega328.hex` que viene dentro del núcleo AVR del IDE de Arduino (`hardware/avr/<versión>/bootloaders`). Ese comando de `avrdude` aún no se ha probado en una placa real.

## Avisos

- **Tensión baja en el puerto.** Con un cable largo o un hub, el puerto puede entregar 4.40 V. En ese caso los LED bajan a unos 1.7 mA y los módulos de 5 V no reciben 4.5 V.
- **Programador ICSP.** Si tu programador alimenta la placa por el pin de 5 V, quita ese jumper cuando el USB esté conectado.
- **A4 y A5.** Tienen resistencias de 4.7 kΩ a 5 V para I2C. No sirven para leer un sensor analógico de alta impedancia.
- **Conector SERIE.** Comparte D0 y D1 con el USB. Un módulo conectado ahí puede impedir que se suba el programa: desconéctalo para programar.
- **RX y TX del conector SERIE.** Los rótulos son los de la placa: el pin RX es la entrada de la placa, así que ahí va el TX del módulo.
- **DIP en ON.** D2 a D9 quedan cargados por el periférico. Si conectas un módulo a uno de esos pines, pon su interruptor en OFF.
- **Servo.** La librería Servo quita el PWM de D9 y D10; con ella, el canal rojo del RGB (D9) ya no se puede atenuar.
- **D13 y SPI.** El LED «L» cuelga de D13, que también es SCK. Un módulo SPI ve esa carga en el reloj.
- **Zumbador.** `tone()` usa el Timer2 y quita el PWM de D3 y D11.
- **3V3.** El pin de 3.3 V sale de un LDO que se calienta: no le pidas más de 50 mA.
- **Consumo.** Con todos los periféricos encendidos la placa consume hasta 143.8 mA; el PTC de 500 mA protege el puerto USB. Ese máximo pasa de los 100 mA que USB permite antes de que el equipo configure el dispositivo; en la práctica los periféricos solo se encienden cuando el programa lo pide.

## Cómo fabricarla

La fuente de verdad son los YAML de `spec/`. Los scripts de `tools/` generan y verifican todo lo demás; con KiCad cerrado:

```powershell
py -3.12 -P tools/gen_hoja.py placas/entrenamiento-328p --todas   # esquemático
py -3.12 -P tools/erc.py placas/entrenamiento-328p                # ERC
powershell -File tools/construir_placa.ps1                        # placa: colocar, rutear, costura, serigrafía (unos 35 min)
py -3.12 -P tools/drc.py placas/entrenamiento-328p                # DRC
py -3.12 -P tools/fab.py placas/entrenamiento-328p                # Gerber, BOM, CPL, PDF
py -3.12 -P tools/verificar_existencias.py placas/entrenamiento-328p
py -3.12 -P tools/modelos3d.py placas/entrenamiento-328p         # modelos 3D sencillos (los asigna a la placa)
py -3.12 -P tools/renders.py placas/entrenamiento-328p            # superior, inferior, isométrico y portada
```

En `fab/v0.1/` quedan `gerbers_v0.1.zip`, `bom_jlc_v0.1.csv`, `cpl_jlc_v0.1.csv`, `esquematico_v0.1.pdf`, `revisar_preview_v0.1.txt` y los PDF de serigrafía a escala 1:1 (`serigrafia_1a1_v0.1_superior.pdf` e `_inferior.pdf`). Sube el zip, la BOM y el CPL a JLCPCB para el análisis DFM; la placa es de 2 capas, FR-4 de 1.6 mm, máscara negra y serigrafía blanca. Los conectores y el potenciómetro (J407, J408, J406, J1, RV301) son de agujero pasante: tras la cotización se decide si JLCPCB los suelda o se sueldan a mano.

## Carpetas

| Carpeta | Contenido |
|---|---|
| `spec/` | YAML de cada hoja y de la placa; `logos/` con el logotipo, Emi y el QR |
| `lib/ayemi.3dshapes/` | Modelos 3D sencillos (`.wrl`) de las seis piezas sin modelo |
| `fab/v0.1/` | Archivos para JLCPCB y serigrafía 1:1 |
| `firmware/prueba_fabrica/` | Firmware de prueba y su `.hex` compilado |
| `wokwi/` | Proyecto de Wokwi (`diagram.json`, `wokwi.toml`, copia del boceto) |
| `docs/` | Diagrama de pines, renders y pruebas manuales |
| `reportes/` | ERC, DRC, existencias y capturas de JLCPCB |

## Licencias

- Hardware (esquemáticos, placa, Gerber, BOM, modelos 3D): CERN-OHL-S-2.0 (`../../LICENSES/CERN-OHL-S-2.0.txt`).
- Firmware y ejemplos: MIT (`firmware/LICENSE` y `../../LICENSES/MIT.txt`).
- Documentación y guías: CC BY-SA 4.0 (`../../LICENSES/CC-BY-SA-4.0.txt`).

Los textos están descargados sin cambios de sus fuentes oficiales; ver `../../LICENSES/LEEME.md`.

El nombre y el logotipo **Ayemi** no se incluyen en ninguna de estas licencias: quedan reservados.

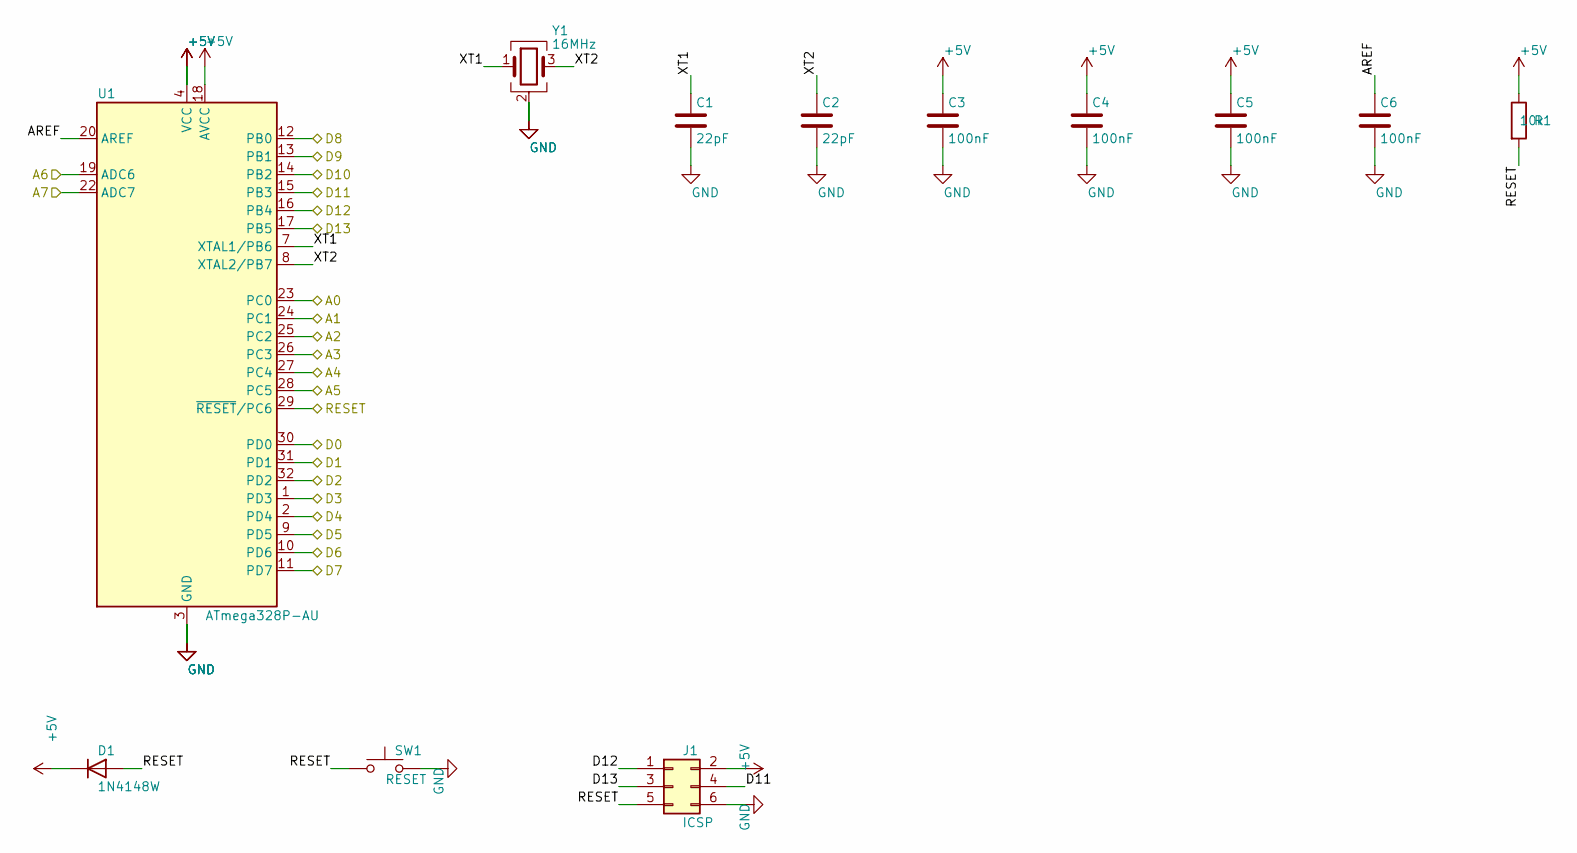
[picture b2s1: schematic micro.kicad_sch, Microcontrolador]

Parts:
C1, C2: 22pF; C_0603_1608Metric; LCSC C1653
C3, C4, C5, C6: 100nF; C_0603_1608Metric; LCSC C14663
D1: 1N4148W; D_SOD-123; LCSC C81598
J1: ICSP; PinHeader_2x03_P2.54mm_Vertical; LCSC C65114
R1: 10k; R_0603_1608Metric; LCSC C25804
SW1: RESET; SW_Push_1TS009xxxx-xxxx-xxxx_6x6x5mm; LCSC C319409
U1: ATmega328P-AU; TQFP-32_7x7mm_P0.8mm; LCSC C14877
Y1: 16MHz; Crystal_SMD_3225-4Pin_3.2x2.5mm; LCSC C70562

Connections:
+5V: C3.1, C4.1, C5.1, D1.1 (K), J1.2, R1.1, U1.4 (VCC), U1.6 (VCC), U1.18 (AVCC); also elsewhere on the board
/A0: U1.23 (PC0); also elsewhere on the board
/A1: U1.24 (PC1); also elsewhere on the board
/A2: U1.25 (PC2); also elsewhere on the board
/A3: U1.26 (PC3); also elsewhere on the board
/A4: U1.27 (PC4); also elsewhere on the board
/A5: U1.28 (PC5); also elsewhere on the board
/A6: U1.19 (ADC6); also elsewhere on the board
/A7: U1.22 (ADC7); also elsewhere on the board
/D0: U1.30 (PD0); also elsewhere on the board
/D1: U1.31 (PD1); also elsewhere on the board
/D2: U1.32 (PD2); also elsewhere on the board
/D3: U1.1 (PD3); also elsewhere on the board
/D4: U1.2 (PD4); also elsewhere on the board
/D5: U1.9 (PD5); also elsewhere on the board
/D6: U1.10 (PD6); also elsewhere on the board
/D7: U1.11 (PD7); also elsewhere on the board
/D8: U1.12 (PB0); also elsewhere on the board
/D9: U1.13 (PB1); also elsewhere on the board
/D10: U1.14 (PB2); also elsewhere on the board
/D11: J1.4, U1.15 (PB3); also elsewhere on the board
/D12: J1.1, U1.16 (PB4); also elsewhere on the board
/D13: J1.3, U1.17 (PB5); also elsewhere on the board
/RESET: D1.2 (A), J1.5, R1.2, SW1.1, U1.29 (~RESET/PC6); also elsewhere on the board
/micro/AREF: C6.1, U1.20 (AREF)
/micro/XT1: C1.1, U1.7 (XTAL1/PB6), Y1.1
/micro/XT2: C2.1, U1.8 (XTAL2/PB7), Y1.3
GND: C1.2, C2.2, C3.2, C4.2, C5.2, C6.2, J1.6, SW1.2, U1.3 (GND), U1.5 (GND), U1.21 (GND), Y1.2 (G), Y1.4 (G); also elsewhere on the board

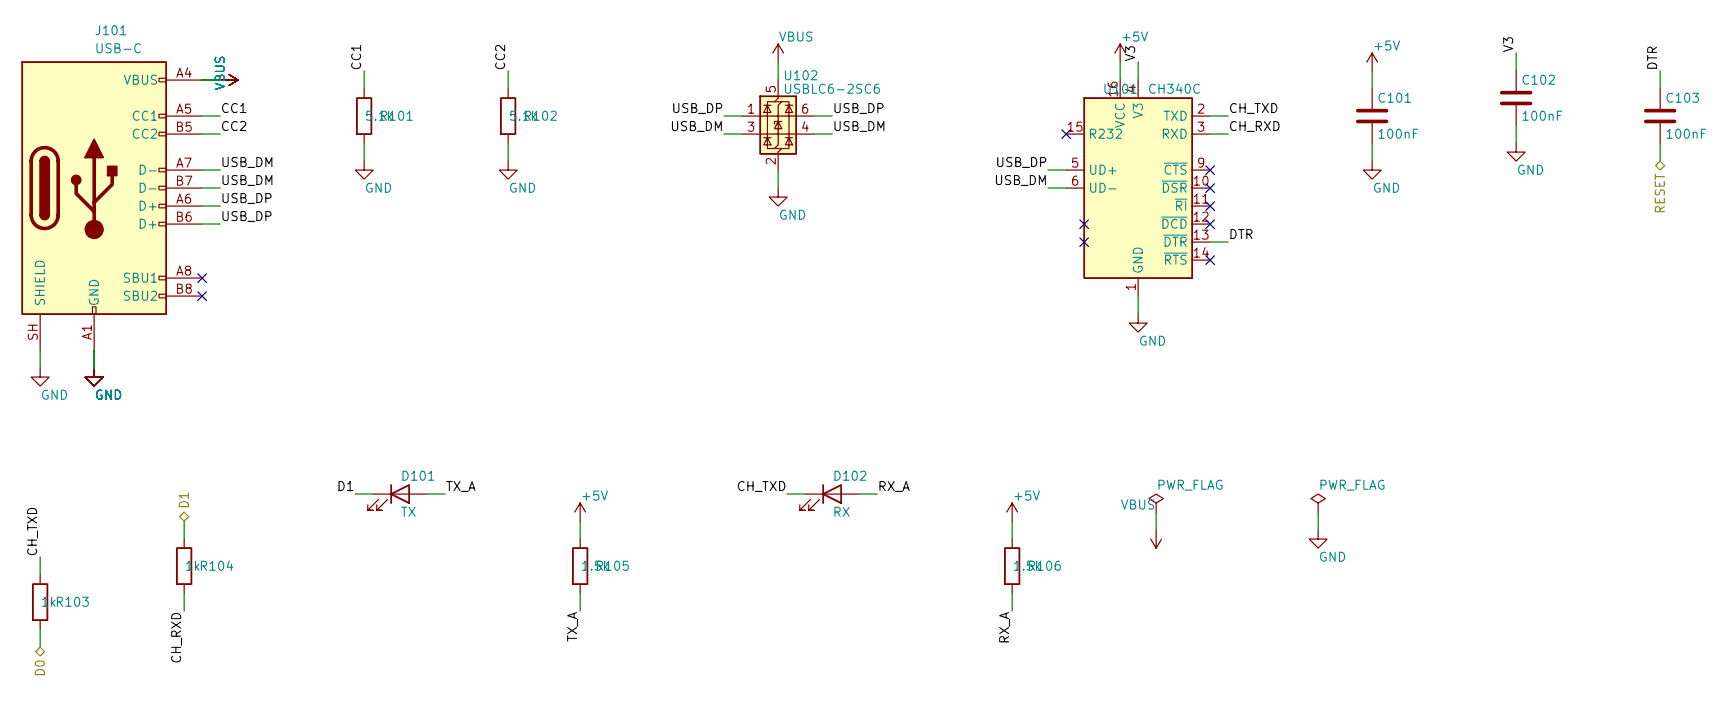
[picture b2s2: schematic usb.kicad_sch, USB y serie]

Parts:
C101, C102, C103: 100nF; C_0603_1608Metric; LCSC C14663
D101: TX; LED_0603_1608Metric; LCSC C2286
D102: RX; LED_0603_1608Metric; LCSC C2286
J101: USB-C; USB_C_Receptacle_HRO_TYPE-C-31-M-12; LCSC C165948
R101, R102: 5.1k; R_0603_1608Metric; LCSC C23186
R103, R104: 1k; R_0603_1608Metric; LCSC C21190
R105, R106: 1.5k; R_0603_1608Metric; LCSC C22843
U101: CH340C; SOIC-16_3.9x9.9mm_P1.27mm; LCSC C84681
U102: USBLC6-2SC6; SOT-23-6; LCSC C7519

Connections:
+5V: C101.1, R105.1, R106.1, U101.16 (VCC); also elsewhere on the board
/D0: R103.2; also elsewhere on the board
/D1: D101.1 (K), R104.1; also elsewhere on the board
/RESET: C103.2; also elsewhere on the board
/usb/CC1: J101.A5 (CC1), R101.1
/usb/CC2: J101.B5 (CC2), R102.1
/usb/CH_RXD: R104.2, U101.3 (RXD)
/usb/CH_TXD: D102.1 (K), R103.1, U101.2 (TXD)
/usb/DTR: C103.1, U101.13 (~DTR)
/usb/RX_A: D102.2 (A), R106.2
/usb/TX_A: D101.2 (A), R105.2
/usb/USB_DM: J101.A7 (D-), J101.B7 (D-), U101.6 (UD-), U102.3 (I/O2), U102.4 (I/O2)
/usb/USB_DP: J101.A6 (D+), J101.B6 (D+), U101.5 (UD+), U102.1 (I/O1), U102.6 (I/O1)
/usb/V3: C102.1, U101.4 (V3)
GND: C101.2, C102.2, J101.A1 (GND), J101.A12 (GND), J101.B1 (GND), J101.B12 (GND), J101.SH (SHIELD), R101.2, R102.2, U101.1 (GND), U102.2 (GND); also elsewhere on the board
VBUS: J101.A4 (VBUS), J101.A9 (VBUS), J101.B4 (VBUS), J101.B9 (VBUS), U102.5 (VBUS); also elsewhere on the board
